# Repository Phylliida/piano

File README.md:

# piano

Open hardware modular hexagonal piano, inspired by the Lumatone.

It is built from identical tiles of 8 x 5 keys on a hex lattice. Each key is
an MX-style magnetic switch over a Hall-effect sensor, so the tile reads how
far every key is pressed. Tiles snap together edge to edge, in any
arrangement, and a short cable under each seam carries power and data. A hub
hangs on a free east edge, takes power in and gives USB out: MIDI and a
serial console with the raw key data.

## Status

| part | state |
|---|---|
| tile PCB | routed, DRC clean, not ordered yet. [`pcb/README.md`](pcb/README.md) lists what to verify before ordering |
| tile case | printed once (2026-11-13): mostly good, but the tray warps a little when the bottom cover goes in. The cover and board need about 1 mm more room; not changed yet |
| hub | circuit, schematic and board done: routed, DRC clean, not reviewed by a person and not ordered. [`hub/README.md`](hub/README.md) lists what to verify before ordering. Its case is designed with the room the tile's print asked for, and its fits are checked on the solids; not printed |
| firmware | tile and hub programs written and tested on a PC, never run on hardware: no board exists yet. Every tile and the hub take new programs through the hub's USB, also only on a PC so far. [`firmware/README.md`](firmware/README.md) |

## Where things are

| file | what |
|---|---|
| `tilegeom.py` | every dimension the board and the case share. Run it to check them |
| `tile_circuit.py` | the tile's circuit as data |
| `gen_lib.py`, `gen_sch.py`, `gen_pcb.py` | make the KiCad library, schematic and (once) the board |
| `route_board.py`, `pcbroute.py` | the board's routing as a script |
| `pcb/` | the KiCad project, and its README with the pin map for the firmware |
| `gen_case.py` | builds the printed case from `tilegeom.py` |
| `hub_circuit.py`, `gen_hub_lib.py`, `gen_hub_sch.py` | the hub's circuit as data, its KiCad library and schematic |
| `hubgeom.py`, `gen_hub_pcb.py`, `route_hub.py` | the hub board's dimensions, the placement of its parts, and its routing as a script |
| `hub/` | the hub's KiCad project, and its README with the pin map for the firmware |
| `gen_hub_case.py` | builds the hub's printed case from `hubgeom.py` |
| `firmware/` | the tile's and the hub's programs, the bootloader, their tests, and the scripts that put programs on every tile and the hub through the hub |
| `cad/` | the output of both case scripts: STLs ready to print, and three drawings |
| `HE60_NOTES.md` | notes on the sensing chain (sections 1 to 5) |

`TILE95.md`, `COST_ESTIMATE.md`, `gen_tile.py`, `gen_hex_board.py`,
`bom_model.py` and `kicad/` belong to earlier designs and contradict this one.

## The case

A printed tray (key plate, ribs, walls) and a printed bottom cover per tile.
No screws.

- **PCB:** drops into the tray from below. The switch pegs locate it.
- **Cover:** tuck its W edge over the lip on the W wall, then press its E edge
  down until the two catch beams click over the bumps on the E wall. Posts on
  the cover press the PCB against the ribs. To open it, pry a beam's tip out
  at its notch in the E wall, beside the E cable channel.
- **Tile to tile:** dovetail rails on a tile's E and N walls run in slots in
  the next tile's W and S walls. One snap latch per seam stops the tile
  lifting off again.
- **Cables:** at every port the cover and both walls are cut away, so the
  cable lies in an open channel from one tile's header to the next one's. It
  goes in from underneath, with the covers on.

### Putting tiles together

1. Start with the south-west tile, keys up, on a table.
2. Lower each further tile straight down beside it: its W and S slots slide
   over the rails of the tiles already there, and the latches click. Tiles
   only go together downward, never sideways.
3. Work outward to the north and east. A tile cannot be lowered into a place
   that already has a tile to its north or east.
4. Turn the keyboard over and plug a 50 mm JST GH 6-pin cable across each
   seam ([`pcb/README.md`](pcb/README.md) says how to measure the 50 mm).
   Either way round works.

To take it apart, unplug the cables and pull tiles straight up, starting at
the north-east. A firm pull releases a latch.

The rails carry a tile's weight, the latches only hold it down. So lift an
assembly by its south-west tile or from underneath; lifted by another tile,
the ones south and west of it hang on their latches.

### The hub

The hub's case is a tray and a cover like a tile's, 45 x 109 mm. Its W wall
is a tile's W wall: two rail slots, a latch window and a cable channel. Its
N wall has the windows for the two USB-C sockets.

- **Where:** on the free E edge of any tile. Lower it onto that tile's rails
  as you would a tile. Nothing joins onto the hub, and the place north-east
  of its tile has to stay empty: a tile there would stand in front of the
  sockets.
- **Board:** drops into the tray from below. The N wall and six small nubs
  locate it.
- **Cover:** tuck its W edge over the lip, then press its E edge down past
  the three tabs in the E wall. To open it, reach into the cable channel
  and pull the cover's edge up there; the tabs give way.
- **Cable:** the same 50 mm cable, from the hub's header to the tile's E
  header, in the channel under the seam.

This case has what the first tile print asked for. The cover stands 1 mm off
every wall, except for six ears 8 mm long: three on the W lip, three on the
tabs' bumps. The board stands 1 mm or more off the W and E walls and the rib
south of it, except at the nubs. The tabs are strips cut free of the E wall,
so they bend and the wall does not. The tile's own case does not have this
yet.

### Printing

`cad/` holds the parts in their print orientation: the tray upside down
(plate on the bed), the cover with its posts up. Print without support. One
tile's tray is 168 x 134 mm.

1. **`plate_test.stl`**, a 1.5 mm plate. Check that switches clip in, measure
   the two spans `gen_case.py` prints, and pass their ratio as `--xy-scale` if
   your printer shrinks.
2. **The coupons:** `coupon_tray.stl` twice, `coupon_cover.stl` and
   `coupon_pcb_dummy.stl` once. A coupon is a 2 x 4-key tile with every snap
   feature of the full one. Check the cover's catch on one, then join the two
   trays E to W and N to S.
3. **`tray.stl`, `cover.stl`** and, until boards exist, **`pcb_dummy.stl`**:
   a plastic stand-in with the board's outline, thickness and peg holes.

4. **The hub:** `hub_tray.stl`, `hub_cover.stl` and, until a board exists,
   `hub_pcb_dummy.stl`, which also has blocks where the two sockets and the
   cable header are. Try it on a full tray: a coupon has a rail where the
   hub has wall.

If a fit is off, change the number in `tilegeom.py` and run `gen_case.py`
again:

| symptom | constant |
|---|---|
| rails too tight or too loose in their slots | `RAIL_CLEAR` (0.15 mm) |
| latch lets go too easily, or will not let go | `LATCH_ANGLE` (50 degrees; higher holds harder) |
| latch does not click in | `LATCH_BITE` (0.6 mm), `LATCH_PLAY` (0.2 mm) |

`LIP_W` and `CATCH_D` must stay as they are: the board's outline is built on
them.

The hub has its own numbers in `hubgeom.py`, for `gen_hub_case.py`:

| symptom | constant |
|---|---|
| cover rattles sideways, or is hard to get in | `EAR_CLEAR` (0.2 mm; the script takes 0.1 to 0.25) |
| board rattles, or will not go in | `NUB_CLEAR` (0.3 mm), `NUB_W` (3 mm) |
| cover bulges, or the board is loose under it | `POST_PRELOAD` (0.1 mm) |
| tabs too stiff or too weak | `TAB_W` (8 mm; narrower is softer) |

Not yet tried in plastic, so expect a round or two on the coupons. Known
soft spots:

- The latch beams stand upright on the bed and bend across their layers,
  the weak direction. They strain 0.7 %, which PLA should take; PETG is
  the safer choice.
- The W lip is a 1.5 mm ledge with nothing under it. Its underside, which
  the cover rests on, will come out rough.
- The dovetails' sharp edges print rounded, which loosens them slightly.
- The hub's tabs also bend across their layers (0.8 % strain), and the
  wall over each USB-C window is a 14 mm bridge.

### Building the case files

```
python3 tilegeom.py     # check the geometry
python3 gen_case.py     # check the fits on the solids, write cad/
python3 hubgeom.py      # the same two steps for the hub
python3 gen_hub_case.py
```

`gen_case.py` needs `manifold3d` and `numpy`. It refuses to write anything
unless the solids show that neighbouring tiles clear each other, that a tile
can be lowered onto its neighbours' rails, that the latches and dovetails
then hold it, and that the cover and the PCB fit. `gen_hub_case.py` does the
same for the hub: its board and cover fit and are held, a USB-C plug fits
each window, and the hub can be lowered onto a tile's E edge, is held there,
leaves the cable's way open and clears the tiles around it.

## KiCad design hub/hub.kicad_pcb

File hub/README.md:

# Hub PCB

The hub hangs on a tile's east edge and plugs into that tile's E port. It
has two USB-C sockets:

- **USB**, to the computer: USB MIDI and a serial console, and the hub's own
  3.3 V.
- **PWR**, from a USB-C charger: the hub asks it for 15 V, for keyboards too
  big for the computer's port to feed.

Like the tile, it is made by scripts, not drawn by hand, and it is fully
routed: KiCad's DRC reports 0 errors and 0 unrouted connections. **No person
has reviewed it, nothing is ordered, and no hub exists yet.**

| file | made by | what |
|---|---|---|
| `../hub_circuit.py` | you | every part and connection, as data |
| `../hubgeom.py` | you | every position the board and the printed case share |
| `hub.kicad_sym`, `hub.pretty/` | `gen_hub_lib.py` | the MCU, eFuse and PD chip symbols and the eFuse's footprint |
| `hub.kicad_sch` | `gen_hub_sch.py` | the schematic |
| `hub.kicad_pcb`, `hub.kicad_pro` | `gen_hub_pcb.py`, then `route_hub.py` | every part placed, the outline, the ground pours, track widths per net (`gen_hub_pcb.py`); every track and via (`route_hub.py`) |
| `../route_hub.py`, `../pcbroute.py` | you | the routing as a script, and the small router it uses |
| `../gen_hub_case.py` | you | the printed case; see the [main README](../README.md) |

Unlike the tile's board, this one can be made again from nothing:

```
./kpython.sh gen_hub_lib.py && ./kpython.sh gen_hub_sch.py     # after a change to hub_circuit.py
REGEN_ROUTED_BOARD=1 ./kpython.sh gen_hub_pcb.py               # place every part: this throws the copper away
./kpython.sh route_hub.py                                      # draw the copper again, about 4 minutes
python3 hubgeom.py && python3 gen_hub_case.py                  # the case, after a change to hubgeom.py
```

Run them from the repository's root. Without `REGEN_ROUTED_BOARD=1` the
placement script refuses to touch a routed board, and `route_hub.py` refuses
a board that already has tracks. A change made by hand in `hub.kicad_sch`
or `hub.kicad_pcb` is lost the next time its script runs. `route_hub.py`
names pins and coordinates, so a moved part or a new one means adapting the
stage that routes it.

## What each run proves

- **Schematic:** KiCad exports its own netlist of the generated file, and it
  must equal `hub_circuit.nets()` net for net (57 nets). Any ERC error stops
  the run. Reruns keep every symbol's UUID, so the board stays linked to its
  schematic.
- **Pins:** every IC connection names the pin it expects
  (`(u.ref, 5, "IN")`), and generation stops if the symbol disagrees.
- **Placement:** every part has a place and the nets the circuit gives it;
  no courtyards overlap; nothing stands where a cover post presses, where
  the cable lies, or on the legs of the lights and buttons on the other
  side; and each chip reads back the way round it was meant to be.
- **Routing:** `route_hub.py` checks every track and via against the net
  classes' clearances as it adds them, then runs DRC with schematic parity
  in a fresh process. Result: 0 errors, 0 parity issues, 0 unrouted
  connections, and 12 silkscreen warnings (reference texts in tight spots).
- **Case:** `gen_hub_case.py` proves on the solids that a board of this
  outline, with the sockets and the cable header where `hubgeom.py` puts
  them, fits the printed case. The placement script takes those places from
  the same file.

What none of this proves: that the circuit is right. The symbols and the
eFuse's footprint were drawn from the datasheets named in `hub_circuit.py`
and `gen_hub_lib.py`, and nobody has checked them a second time. The tile's
board had such a review; this one has not.

## The board

39.3 x 78.0 mm, 2 layers, 1.6 mm. 74 parts, two of them pads that stay
empty (SWD and a spare serial port).

- **Back:** every part but four. North, the two sockets, opening north
  through the case's wall: under USB its protection, the 3.3 V regulator
  and its eFuse; under PWR the PD chip and its eFuse. Across the middle the
  cable channel, bare, with the tile port at its east end. South of it the
  MCU, its crystal and the ADC's dividers. At the south end the debug pads.
- **Front (the plate side):** two 3 mm LEDs (STATUS, POWER) and two push
  buttons (USER, BOOT), through-hole, in a row near the south end. They
  reach through holes in the case's plate. BOOT ends flush with the plate,
  so only a pen tip presses it; USER stands 2.3 mm proud.
- **Rule areas on the back:** an octagon where each of the case's four
  cover posts presses, and a strip where the cable lies. DRC keeps parts
  off them.

### Power

Two inputs, one output: `VIN`, the tiles' supply, on the cable.

- Each input reaches `VIN` through its own eFuse (TPS259470A), which
  switches it, ramps it up slowly, limits its current and reports that
  current to the ADC.
  - PWR: up to 2.02 A, the most a tile port's two contacts carry. Cut off
    above 17.8 V, so a charger that offers only 20 V cannot overrun the
    tiles' 20 V limit.
  - USB: 0.5 A, what any USB port may be asked for; 1.43 A while the
    socket's CC pins say the port offers 1.5 A or more (the firmware pulls
    `ILIM_HI` low).
- Each eFuse blocks reverse current, so the two inputs can never feed each
  other, whatever the firmware does.
- Both eFuses' enables are pulled low: the tiles stay off until the
  firmware switches one on.
- The MCU runs from the computer's USB only, through a TLV75733. With a
  charger alone the hub is off, and so are the tiles.
- The PD chip (CH224A) asks for 15 V by its `CFG1` resistor (56k) as soon
  as a charger is there. The firmware reads over I2C what was agreed and
  can ask for less.
- A SMAJ20A on `V_PD` and one on `VIN`, as on the tiles.

What the firmware does with all this is in
[`../firmware/DESIGN.md`](../firmware/DESIGN.md), "Power".

### The tile port

The same JST GH header, pinout and 220R series resistors as a tile's own
ports ([`../pcb/README.md`](../pcb/README.md)), so the hub looks like one
more tile to the cable. The header's opening is 50 mm from the opening of
the tile's E header when the hub hangs on that tile: the same 50 mm cable.

## How it is routed

`route_hub.py` works in stages. The first eight name their tracks'
coordinates; `signals` searches for its own.

| stage | what it adds |
|---|---|
| `fine` | The eFuses: 0.2 mm tracks out of their side pins and short necks out of their power strips, which stand 0.2 mm from their neighbours. |
| `usb` | The USB socket: the CC resistors, and the data pair through its protection and down to the MCU. |
| `pd` | The charger's socket and the PD chip under it. |
| `power` | VBUS, V_PD and VIN, up to 1 mm wide, on the back: from the sockets to the eFuses, and VIN along the cable channel's north edge to the tile port. The regulator and the 3.3 V trunk. |
| `mcu` | The MCU's supply and ground pins and their capacitors. |
| `near` | What joins neighbours: the LEDs, the buttons, the crystal, the three dividers beside the MCU, the two lines to the tile port. |
| `escapes` | A short track and a via at each pad that the back's copper shuts in, for the long runs to start and end on. |
| `gnd` | A via to the front's pour at every ground pad. |
| `signals` | The 23 nets left, searched net by net, the short ones first, on whichever side has room. A net that finds no way makes room by taking one neighbour out and laying both again. About three minutes. |
| `ties` | Vias between the two pours where the tracks cut either into pieces, and a way through to any piece of ground still on its own. |

The result: 0.99 m of track on the back, 0.59 m on the front, 179 vias, 95
of them ground.

Weak spots, accepted for now:

- **The front is not an unbroken ground plane.** The back is full round the
  chips, so the searched runs go over the front wherever they have to cross
  something. Round the MCU they cut the front's pour into one large part
  and a few small ones, which `ties` joins through the back's.
- **The searched runs are valid, not tidy.** They keep every clearance and
  DRC passes, but they wander. Eleven other settings of the search (a
  dearer front, other via costs) did no better. A tidier board needs
  explicit routes for the long runs, or a different placement.
- **The USB data pair is not impedance controlled:** two 0.2 mm tracks, 44
  and 47 mm long, one of them with a 4 mm hop over the front, because the
  socket's pads are laid out so that one cannot stay on the back. This is
  full-speed USB (12 Mbit/s), where runs this short are usual practice; it
  has not been measured.

Two places differ from the first placement, both so that ground pads get
their vias: the tile port's two series resistors stand 1.1 mm further east
(`LINK_R_X`), and the three divider rows are 2.2 mm apart instead of 1.5.

## Pin map, for the firmware

`hub_circuit.py` is the truth (`PINS` and the constants under it);
`../firmware/hub/board.h` and this table are copies.

| net | pin | what |
|---|---|---|
| `USB_DM`, `USB_DP` | 44 PA11, 45 PA12 | OTGFS1, also the ROM bootloader's USB DFU |
| `LINK_TX`, `LINK_RX` | 16 PA2, 17 PA3 | USART2, the cable to the tile: wire A and wire B, each through 220R |
| `AUX_TX`, `AUX_RX` | 51 PC10, 52 PC11 | USART3, on the AUX pads (not fitted); a ROM bootloader UART |
| `PD_SCL`, `PD_SDA` | 58 PB6, 59 PB7 | I2C1 to the CH224A, through 1k; the chip pulls them up itself |
| `PD_PG` | 57 PB5 | low = the charger agreed. Open drain, 100k to 3.3 V |
| `EN_PD`, `EN_HOST` | 30 PB12, 32 PB13 | high = eFuse on. 100k to ground each |
| `ILIM_HI` | 28 PB2 | open drain: low = 1.43 A from USB, open = 0.5 A |
| `FLT_PD`, `FLT_HOST` | 61 PB8, 62 PB9 | low = fault. Open drain, 100k to 3.3 V each |
| `VIN_SENSE` | 8 PC0, ADC1 channel 10 | VIN through 100k / 15k, 100n |
| `VPD_SENSE` | 9 PC1, channel 11 | V_PD through 100k / 15k, 100n |
| `VBUS_SENSE` | 10 PC2, channel 12 | VBUS through 100k / 100k, 100n |
| `IMON_PD` | 11 PC3, channel 13 | the PD eFuse's ILM pin, through 10k |
| `IMON_HOST` | 14 PA0, channel 0 | the USB eFuse's ILM pin, through 10k |
| `CC1_SENSE`, `CC2_SENSE` | 15 PA1, 20 PA4, channels 1 and 4 | the USB socket's CC pins, through 10k |
| `LED_STATUS`, `LED_POWER` | 37 PC6, 38 PC7 | high = lit, through 470R |
| `BTN_USER` | 2 PC13 | low = pressed. 10k to 3.3 V |
| `SWDIO`, `SWCLK` | 46 PA13, 49 PA14 | the debug pads |
| `BOOT0` | 60 PF11 | 3.3k to ground; the BOOT button to 3.3 V |

- **Current:** an eFuse's ILM pin gives 182 µA per amp into its resistor:
  1.65k on the PD path (limit 2.02 A), 6.65k on the USB path (0.50 A), with
  3.6k beside it while `ILIM_HI` is low (1.43 A).
- **Debug pads J1**, pad 1 to 6, as on a tile: +3V3, BOOT0, SWCLK, NRST,
  SWDIO, GND. **AUX pads J5**, pad 1 to 3: GND, AUX_TX, AUX_RX.
- **Crystal:** 12 MHz, as on a tile.

## Before ordering: not yet verified

- **A review by a person.** Start with the two symbols and the footprint
  drawn here: the TPS259470A (pins and the RPW0010A land pattern) and the
  CH224A, against their datasheets. Then the USB-C sockets' pad order, the
  LEDs' polarity, and the two buttons' heights against the case's plate.
- **LCSC part numbers:** only the CH224A (`C42459160`) and the TPS259470A
  (`C3662799`) have one. Still to pick:
  AT32F405RCT7, the 12 MHz crystal, TLV75733PDBV, BLM18PG221SN1D,
  USBLC6-2SC6, SMAJ20A, the two TYPE-C-31-M-12 sockets, the JST GH header
  (see the tile's README on the clone), the 3 mm LEDs, the two 6 mm push
  buttons (5 mm and 7.3 mm tall), and every resistor and capacitor. The
  capacitor values carry their voltage ratings (`1u/50V`): keep them.
- **LED colour:** red or green. Blue and white ones need about 3 V, too
  much for a 3.3 V pin through 470R.
- **Nothing has run on hardware.** The firmware for this board passes its
  tests on a PC ([`../firmware/README.md`](../firmware/README.md)).
- **A blank tile's first program.** The ROM bootloader of a tile listens on
  its W and S ports; the hub's box hangs on an E edge. So a tile's first
  flashing needs the hub's cable in that tile's W or S port, with the hub
  loose beside it, and the tile's BOOT0 pads bridged; or SWD. Every later
  program comes through the hub wherever the tile is. Changing this would
  be a change to the tile's hardware, and is not decided.

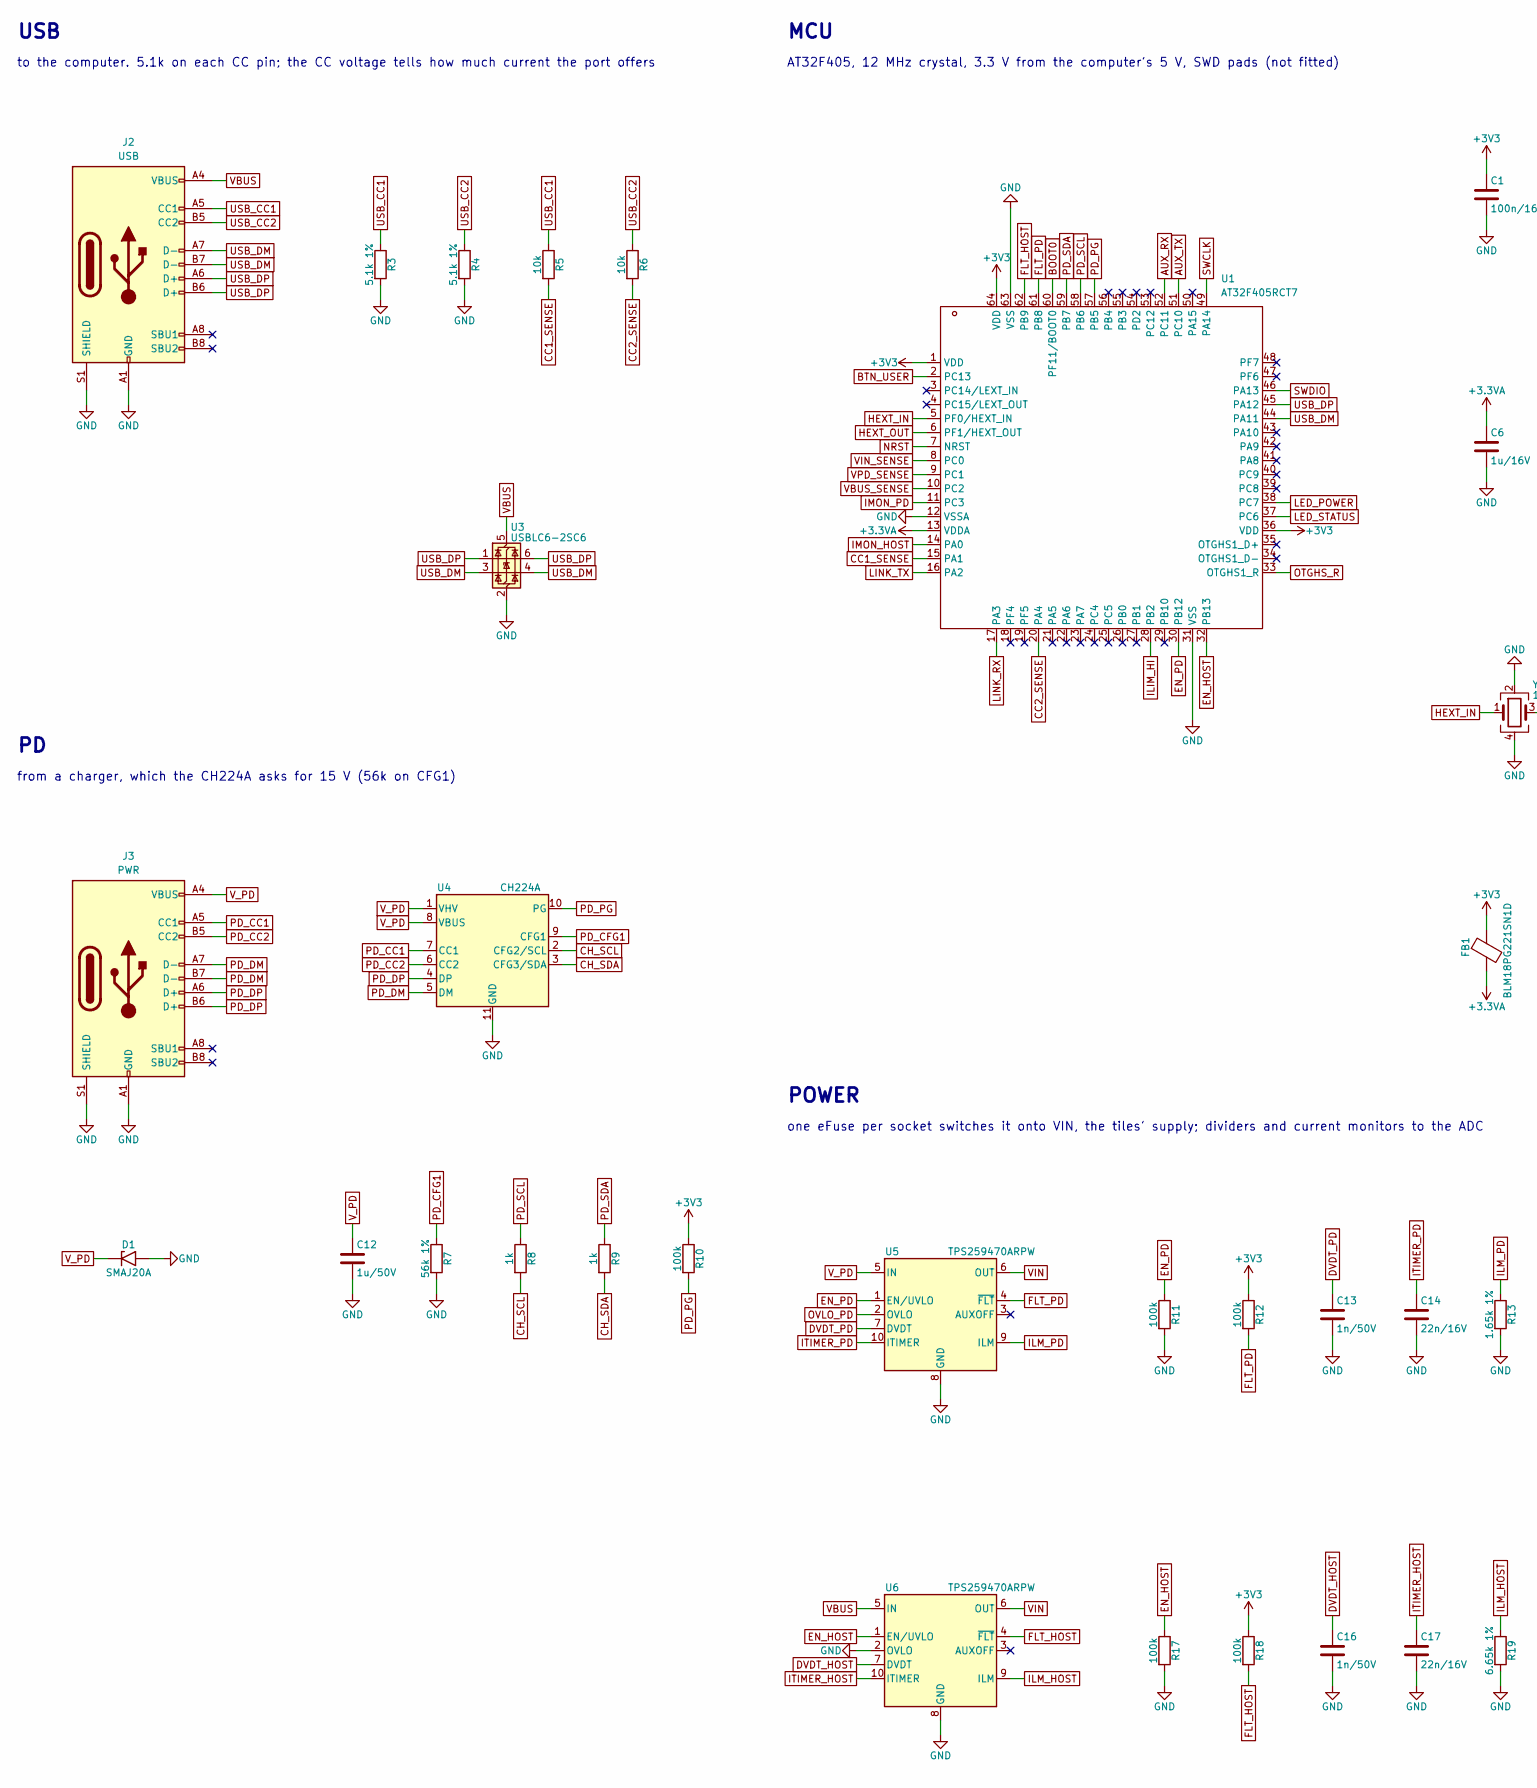
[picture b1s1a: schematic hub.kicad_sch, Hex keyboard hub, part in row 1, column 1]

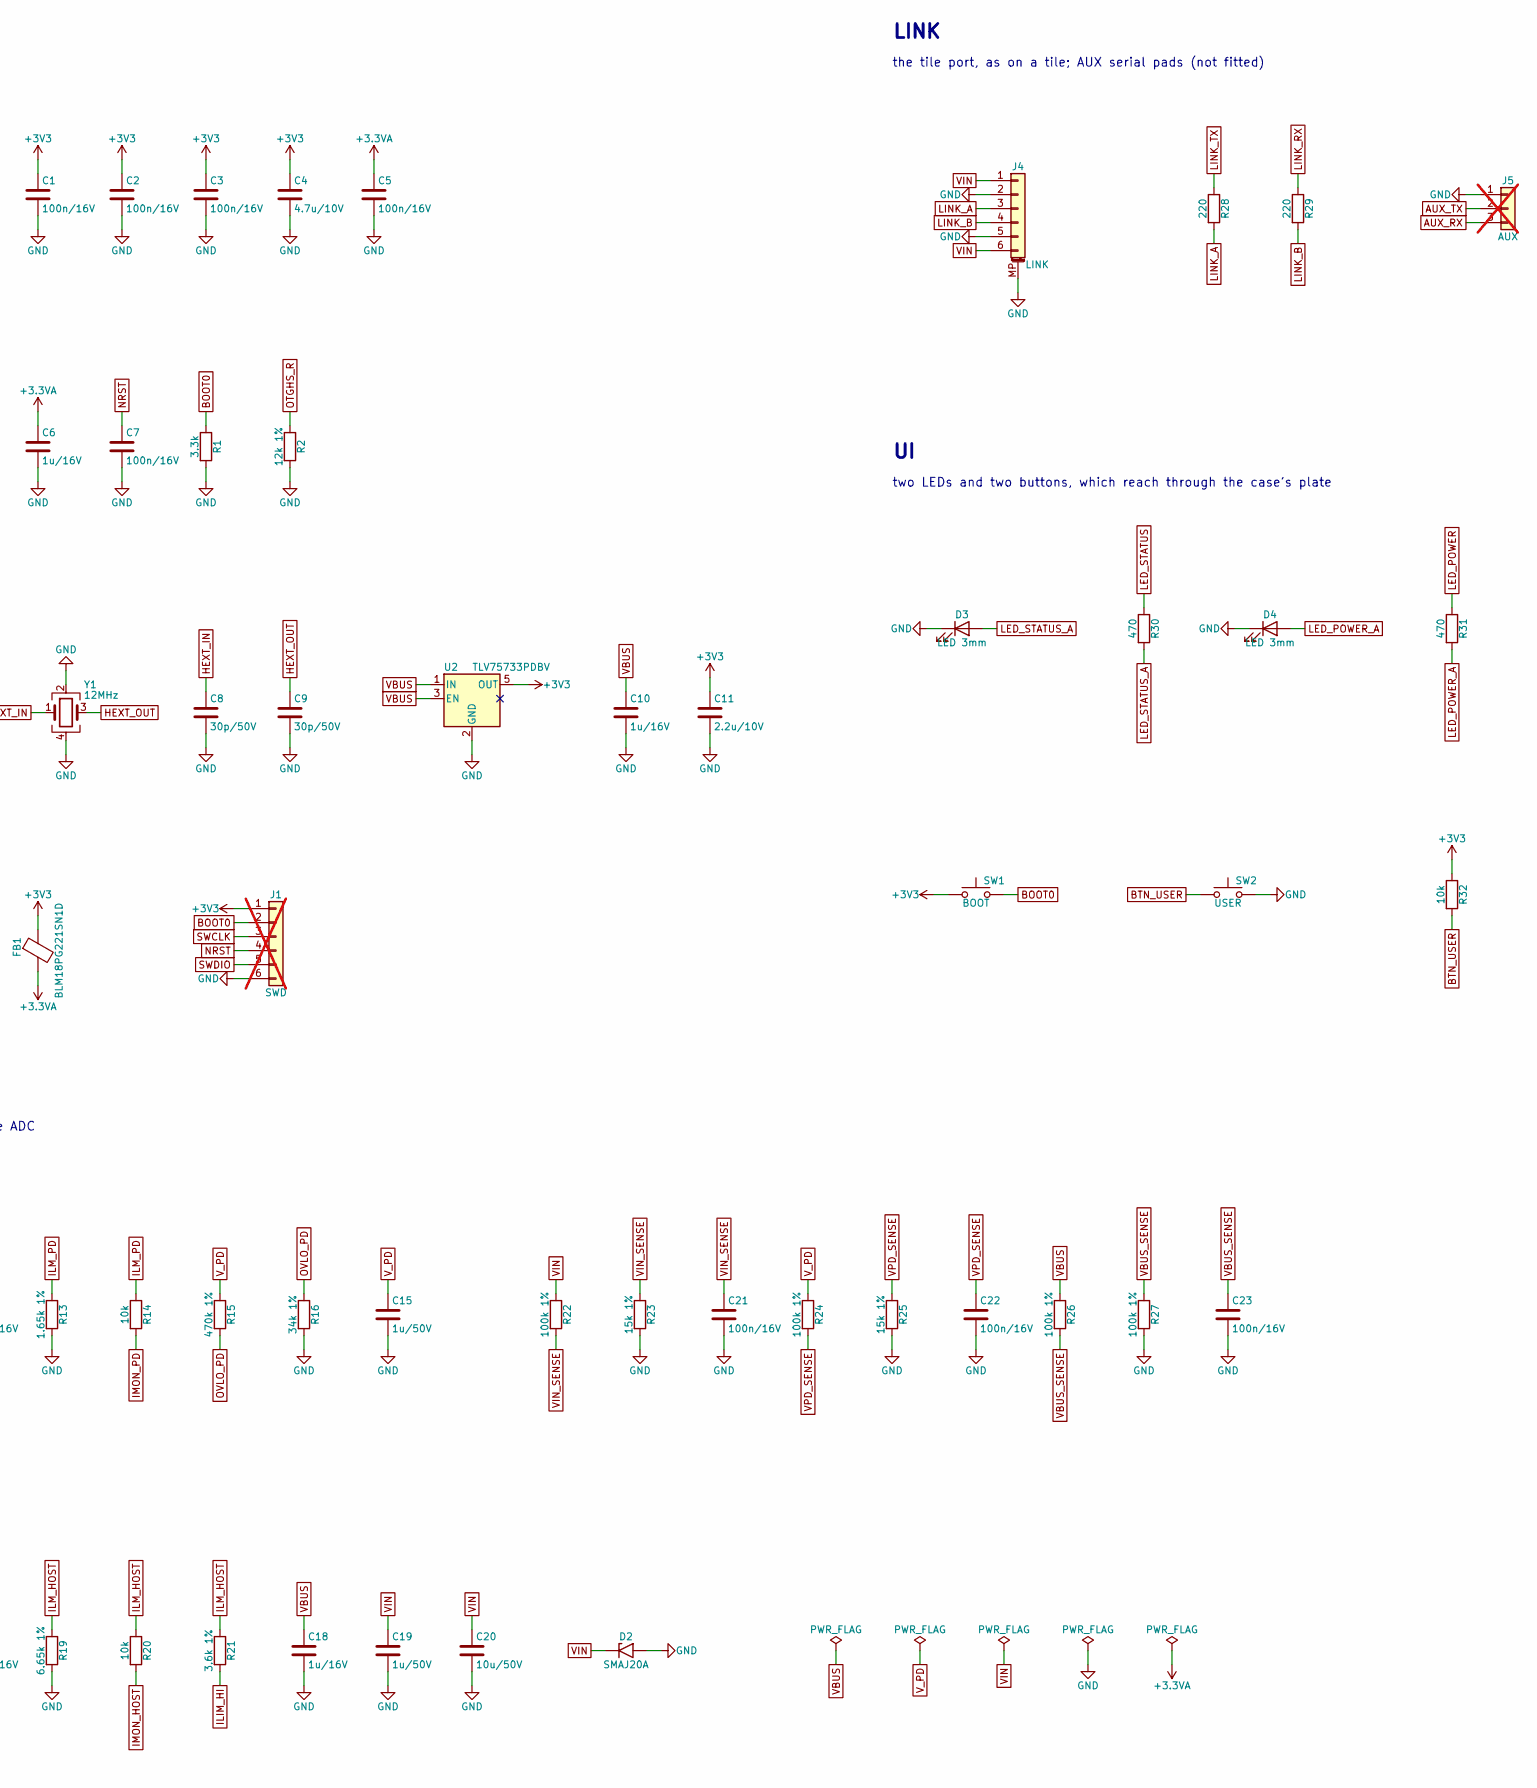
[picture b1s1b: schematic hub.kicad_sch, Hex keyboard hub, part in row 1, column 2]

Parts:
C1, C2, C3, C5, C7, C21, C22, C23: 100n/16V; C_0402_1005Metric
C4: 4.7u/10V; C_0603_1608Metric
C6, C10, C18: 1u/16V; C_0402_1005Metric
C8, C9: 30p/50V; C_0402_1005Metric
C11: 2.2u/10V; C_0603_1608Metric
C12, C15, C19: 1u/50V; C_0603_1608Metric
C13, C16: 1n/50V; C_0402_1005Metric
C14, C17: 22n/16V; C_0402_1005Metric
C20: 10u/50V; C_1206_3216Metric
D1, D2: SMAJ20A; D_SMA
D3, D4: LED 3mm; LED_D3.0mm
FB1: BLM18PG221SN1D; L_0603_1608Metric; MPN BLM18PG221SN1D
J1: SWD; PinHeader_1x06_P2.54mm_Vertical_SMD_Pin1Left; not fitted
J2: USB; USB_C_Receptacle_HRO_TYPE-C-31-M-12; MPN TYPE-C-31-M-12
J3: PWR; USB_C_Receptacle_HRO_TYPE-C-31-M-12; MPN TYPE-C-31-M-12
J4: LINK; JST_GH_SM06B-GHS-TB_1x06-1MP_P1.25mm_Horizontal; MPN SM06B-GHS-TB
J5: AUX; PinHeader_1x03_P2.54mm_Vertical_SMD_Pin1Left; not fitted
R1: 3.3k; R_0402_1005Metric
R2: 12k 1%; R_0402_1005Metric
R3, R4: 5.1k 1%; R_0402_1005Metric
R5, R6, R14, R20, R32: 10k; R_0402_1005Metric
R7: 56k 1%; R_0402_1005Metric
R8, R9: 1k; R_0402_1005Metric
R10, R11, R12, R17, R18: 100k; R_0402_1005Metric
R13: 1.65k 1%; R_0402_1005Metric
R15: 470k 1%; R_0402_1005Metric
R16: 34k 1%; R_0402_1005Metric
R19: 6.65k 1%; R_0402_1005Metric
R21: 3.6k 1%; R_0402_1005Metric
R22, R24, R26, R27: 100k 1%; R_0402_1005Metric
R23, R25: 15k 1%; R_0402_1005Metric
R28, R29: 220; R_0402_1005Metric
R30, R31: 470; R_0402_1005Metric
SW1: BOOT; SW_PUSH_6mm_H5mm
SW2: USER; SW_PUSH_6mm_H7.3mm
U1: AT32F405RCT7; LQFP-64_10x10mm_P0.5mm; MPN AT32F405RCT7
U2: TLV75733PDBV; SOT-23-5
U3: USBLC6-2SC6; SOT-23-6
U4: CH224A; SSOP-10-1EP_3.9x4.9mm_P1mm_EP2.1x3.3mm; MPN CH224A; LCSC C42459160
U5, U6: TPS259470ARPW; TI_RPW0010A_QFN-10_2x2mm; MPN TPS259470ARPWR; LCSC C3662799
Y1: 12MHz; Crystal_SMD_3225-4Pin_3.2x2.5mm; MPN X322512MSB4SI

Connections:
+3.3VA: C5.1, C6.1, FB1.2, U1.13 (VDDA)
+3V3: C1.1, C2.1, C3.1, C4.1, C11.1, FB1.1, J1.1, R10.1, R12.1, R18.1, R32.1, SW1.1, U1.1 (VDD), U1.36 (VDD), U1.64 (VDD), U2.5 (OUT)
AUX_RX: J5.3, U1.52 (PC11)
AUX_TX: J5.2, U1.51 (PC10)
BOOT0: J1.2, R1.1, SW1.2, U1.60 (PF11/BOOT0)
BTN_USER: R32.2, SW2.1, U1.2 (PC13)
CC1_SENSE: R5.2, U1.15 (PA1)
CC2_SENSE: R6.2, U1.20 (PA4)
CH_SCL: R8.2, U4.2 (CFG2/SCL)
CH_SDA: R9.2, U4.3 (CFG3/SDA)
DVDT_HOST: C16.1, U6.7 (DVDT)
DVDT_PD: C13.1, U5.7 (DVDT)
EN_HOST: R17.1, U1.32 (PB13), U6.1 (EN/UVLO)
EN_PD: R11.1, U1.30 (PB12), U5.1 (EN/UVLO)
FLT_HOST: R18.2, U1.62 (PB9), U6.4 (~FLT)
FLT_PD: R12.2, U1.61 (PB8), U5.4 (~FLT)
GND: C1.2, C2.2, C3.2, C4.2, C5.2, C6.2, C7.2, C8.2, C9.2, C10.2, C11.2, C12.2, C13.2, C14.2, C15.2, C16.2, C17.2, C18.2, C19.2, C20.2, C21.2, C22.2, C23.2, D1.2 (A2), D2.2 (A2), D3.1 (K), D4.1 (K), J1.6, J2.A1 (GND), J2.A12 (GND), J2.B1 (GND), J2.B12 (GND), J2.S1 (SHIELD), J3.A1 (GND), J3.A12 (GND), J3.B1 (GND), J3.B12 (GND), J3.S1 (SHIELD), J4.2, J4.5, J4.MP (MountPin), J5.1, R1.2, R2.2, R3.2, R4.2, R7.2, R11.2, R13.2, R16.2, R17.2, R19.2, R23.2, R25.2, R27.2, SW2.2, U1.12 (VSSA), U1.31 (VSS), U1.63 (VSS), U2.2 (GND), U3.2 (GND), U4.11 (GND), U5.8 (GND), U6.2 (OVLO), U6.8 (GND), Y1.2, Y1.4
HEXT_IN: C8.1, U1.5 (PF0/HEXT_IN), Y1.1
HEXT_OUT: C9.1, U1.6 (PF1/HEXT_OUT), Y1.3
ILIM_HI: R21.2, U1.28 (PB2)
ILM_HOST: R19.1, R20.1, R21.1, U6.9 (ILM)
ILM_PD: R13.1, R14.1, U5.9 (ILM)
IMON_HOST: R20.2, U1.14 (PA0)
IMON_PD: R14.2, U1.11 (PC3)
ITIMER_HOST: C17.1, U6.10 (ITIMER)
ITIMER_PD: C14.1, U5.10 (ITIMER)
LED_POWER: R31.1, U1.38 (PC7)
LED_POWER_A: D4.2 (A), R31.2
LED_STATUS: R30.1, U1.37 (PC6)
LED_STATUS_A: D3.2 (A), R30.2
LINK_A: J4.3, R28.2
LINK_B: J4.4, R29.2
LINK_RX: R29.1, U1.17 (PA3)
LINK_TX: R28.1, U1.16 (PA2)
NRST: C7.1, J1.4, U1.7 (NRST)
OTGHS_R: R2.1, U1.33 (OTGHS1_R)
OVLO_PD: R15.2, R16.1, U5.2 (OVLO)
PD_CC1: J3.A5 (CC1), U4.7 (CC1)
PD_CC2: J3.B5 (CC2), U4.6 (CC2)
PD_CFG1: R7.1, U4.9 (CFG1)
PD_DM: J3.A7 (D-), J3.B7 (D-), U4.5 (DM)
PD_DP: J3.A6 (D+), J3.B6 (D+), U4.4 (DP)
PD_PG: R10.2, U1.57 (PB5), U4.10 (PG)
PD_SCL: R8.1, U1.58 (PB6)
PD_SDA: R9.1, U1.59 (PB7)
SWCLK: J1.3, U1.49 (PA14)
SWDIO: J1.5, U1.46 (PA13)
USB_CC1: J2.A5 (CC1), R3.1, R5.1
USB_CC2: J2.B5 (CC2), R4.1, R6.1
USB_DM: J2.A7 (D-), J2.B7 (D-), U1.44 (PA11), U3.3 (I/O2), U3.4 (I/O2)
USB_DP: J2.A6 (D+), J2.B6 (D+), U1.45 (PA12), U3.1 (I/O1), U3.6 (I/O1)
VBUS: C10.1, C18.1, J2.A4 (VBUS), J2.A9 (VBUS), J2.B4 (VBUS), J2.B9 (VBUS), R26.1, U2.1 (IN), U2.3 (EN), U3.5 (VBUS), U6.5 (IN)
VBUS_SENSE: C23.1, R26.2, R27.1, U1.10 (PC2)
VIN: C19.1, C20.1, D2.1 (A1), J4.1, J4.6, R22.1, U5.6 (OUT), U6.6 (OUT)
VIN_SENSE: C21.1, R22.2, R23.1, U1.8 (PC0)
VPD_SENSE: C22.1, R24.2, R25.1, U1.9 (PC1)
V_PD: C12.1, C15.1, D1.1 (A1), J3.A4 (VBUS), J3.A9 (VBUS), J3.B4 (VBUS), J3.B9 (VBUS), R15.1, R24.1, U4.1 (VHV), U4.8 (VBUS), U5.5 (IN)

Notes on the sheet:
USB
to the computer. 5.1k on each CC pin; the CC voltage tells how much current the port offers
from a charger, which the CH224A asks for 15 V (56k on CFG1)
MCU
AT32F405, 12 MHz crystal, 3.3 V from the computer's 5 V, SWD pads (not fitted)
POWER
one eFuse per socket switches it onto VIN, the tiles' supply; dividers and current monitors to the ADC
LINK
the tile port, as on a tile; AUX serial pads (not fitted)
two LEDs and two buttons, which reach through the case's plate

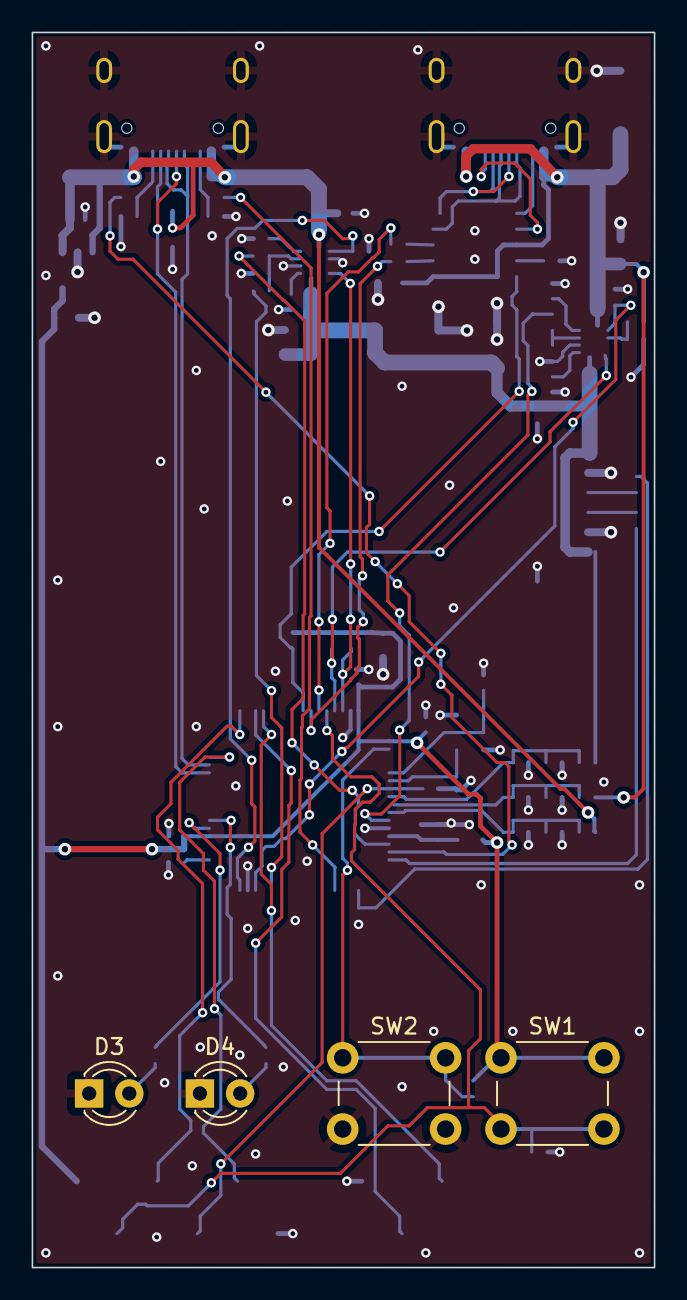
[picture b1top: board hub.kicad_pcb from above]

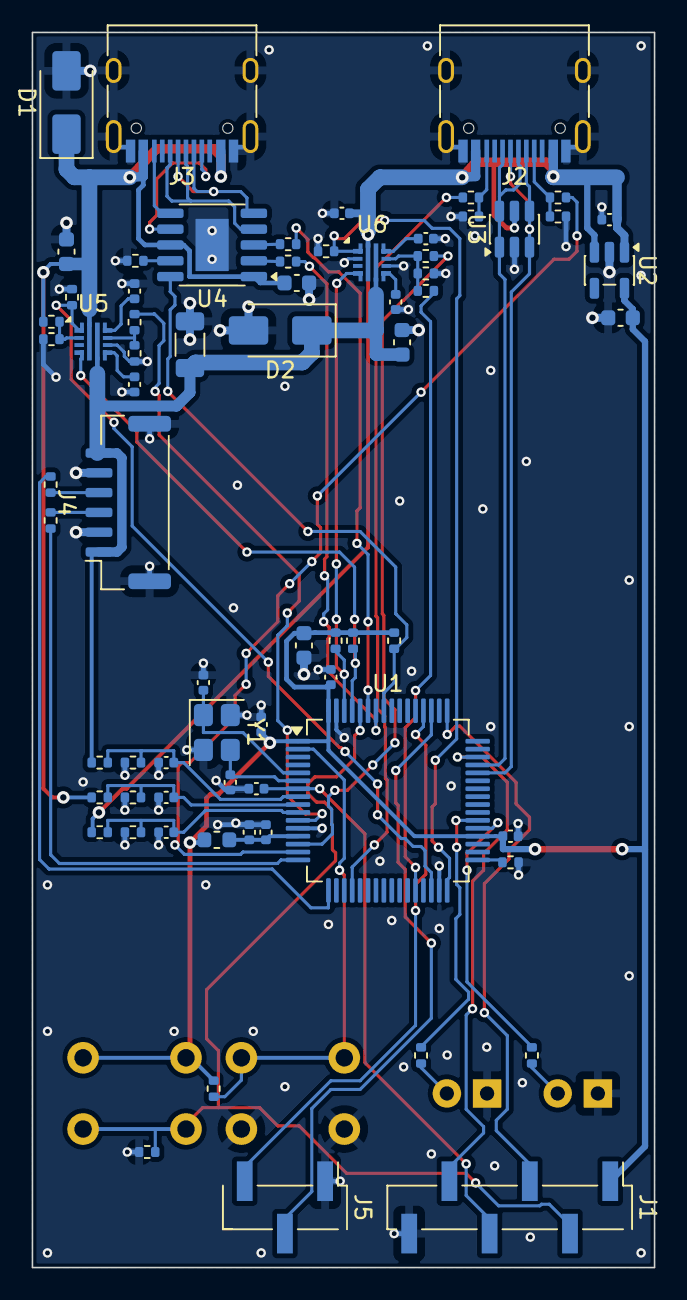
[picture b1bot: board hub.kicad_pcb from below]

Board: 2 copper layers, 39.3 x 78.0 mm, 74 parts (70 on the bottom side), 57 nets.
